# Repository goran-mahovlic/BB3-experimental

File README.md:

View this project on [CADLAB.io](https://cadlab.io/project/24226). 

# BB3-experimental
Experimental PCBs for BB3

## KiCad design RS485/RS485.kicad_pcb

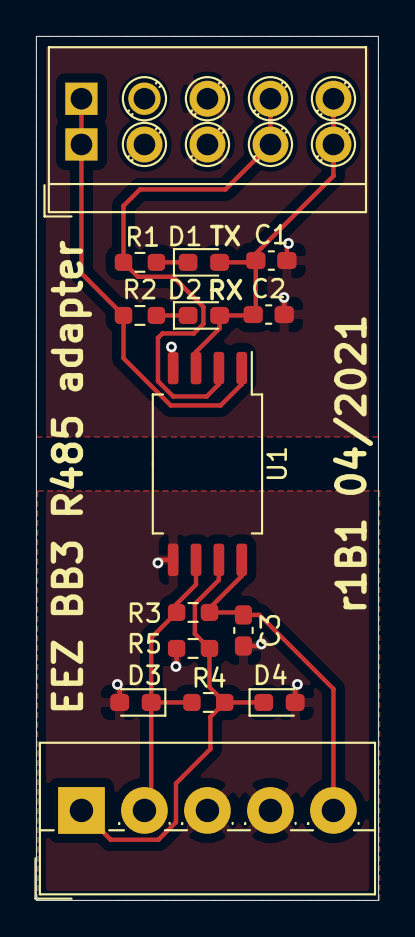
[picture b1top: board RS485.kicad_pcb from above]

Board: 2 copper layers, 19.0 x 48.0 mm, 15 parts (0 on the bottom side), 10 nets.

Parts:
C1: 10n; C_0603_1608Metric_Pad1.08x0.95mm_HandSolder
C2, C3: 100n; C_0603_1608Metric_Pad1.08x0.95mm_HandSolder
D1, D2: LED; LED_0603_1608Metric_Pad1.05x0.95mm_HandSolder
D3, D4: 82356050101; D_0603_1608Metric_Pad1.05x0.95mm_HandSolder
J1: 15EDGA-3.5-05P-14-00AH
J2: Conn_01x05; TerminalBlock_4Ucon_1x05_P3.50mm_Vertical
R1, R2: 300; R_0603_1608Metric_Pad0.98x0.95mm_HandSolder
R3: PU; R_0603_1608Metric_Pad0.98x0.95mm_HandSolder
R4: RT; R_0603_1608Metric_Pad0.98x0.95mm_HandSolder
R5: PD; R_0603_1608Metric_Pad0.98x0.95mm_HandSolder
U1: MAX22025FAWA+; SOIC-8_7.5x5.85mm_P1.27mm

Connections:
+3V3: C1.1, C2.1, D1.2, D2.2, J1.9, J1.10, U1.3
+5V: C3.1, J2.5, R3.2, U1.8
/A: D3.1, J2.2, R3.1, R4.2, U1.6
/B: D4.1, J2.1, R4.1, R5.2, U1.7
/RX: J1.1, J1.2, R2.1, U1.1
/TX: J1.7, J1.8, R1.2, U1.2
GND1: C1.2, C2.2, J1.5, J1.6, U1.4
GND2: C3.2, D3.2, D4.2, J2.3, J2.4, R5.1, U1.5
unnamed: D1.1, R1.1
unnamed: D2.1, R2.2

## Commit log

2020-11-03 Initial schematics, and PCB
2020-11-03 Removing old library
2020-11-03 Finished routing, adding pictures and README
2020-11-03 Removing not needed files
2020-11-04 More cooper on power lines
2020-12-26 Changing pinout
2020-12-26 Changing pinout fix #3 fix #1
2020-12-26 Routing, adding mounting holesFix #2
2020-12-26 Updating pictures
2021-01-13 Adding new production files
2021-04-07 Adding RS485 board
2021-04-25 Backlink to CADLAB.io has been added.
2021-09-15 Adding v3
